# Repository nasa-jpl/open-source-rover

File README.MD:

# JPL Open Source Rover Project
The JPL Open Source Rover is an open source, build it yourself, scaled down version of the 6 wheel rover design that JPL uses to explore the surface of Mars. The Open Source Rover is designed almost entirely out of consumer off the shelf (COTS) parts. This project is intended to be a teaching and learning experience for those who want to get involved in mechanical engineering, software, electronics, or robotics.

## About the Project

### Motivation
JPL is always looking to inspire the next generation of scientists, engineers, and roboticists to help us explore and learn about our solar system (and beyond!). We release the plans for this rover as a way to try and give budding enthusiasts a fun robotics project that will help teach them and get them involved in robotics sooner and at a lower cost. 

### Specifications & Technical Attributes

The specific attributes of the robot you build will depend slightly on the type of electronics and motors you buy for the system.  The numbers shown below are for the version of the robot that contains exactly the parts that we suggest in our build documents and parts list. Below, you can see which parts could be changed for which spec upgrades.

| Attribute	                                | Value [imperial]         | Value [SI]             |
| ----------                                |:-----:                   | :-------------:        |
| Weight                                    | 28 [lbs]                 | 12.7 [kg]              |
| Footprint                                 | 24x14 [in]               | 60.96x30.48 [cm]       |
| Battery Capacity                          | 5200 [mAh]               | 5200 [mAh]             |
| Battery Discharge Rate                    | 8 [A]                    | 8 [A]                  |
| Nominal Current Draw                      | 1.2 [A]                  | 1.2 [A]                |
| Operating time                            | 5 [hrs] (continual use)  | 5 [hrs] (continual use)|
| Approximate Max speed                     | 68.8 [in/s]              | 1.75 [m/s]             |
| Maximum 90 deg vertical scale             | 12 [in]                  | 30.48 [cm]             | 
| Maximum height differential between sides | 14 [in]                  | 35.56 [cm]             |
| Communication (in this guide)             | Bluetooth app (Android only) and Xbox Controller| |
| Cost                                      | ~ $2,500                 |                        |

Again, the above statistics depend on which components you select when buying parts. One potential change is for the motors; you can, for example, select higher RPM motors (to drive your rover faster) at the sacrifice of max stall torque, which would potentially limit your rover's ability to climb. A selection of motors that would integrate easily with the rest of the suggested rover design can be found at [GoBilda](https://www.gobilda.com/5202-series-yellow-jacket-planetary-gear-motors/).

### Features
This rover is designed to function similarly to the 6 wheel rover designs on Mars and employs a few of the major driving mechanics that the mars rovers use to traverse rocky surfaces:
 * __Rocker-Bogie:__ The Rocker-Bogie suspension system allows all 6 wheels to continually be in contact with the ground while climbing over obstacles
 * __Differential Pivot:__ Allows weight to be mechanically offloaded from one side of the rover to the other while climbing
 * __6-Wheel Ackerman Steering:__ Driving and steering/turning mechanism that governs where the wheels point and how fast each of them will move.

We chose a Raspberry Pi to be the "brain" of this rover for its versatility, accessibility, simplicity, and ability to add and upgrade your own modifications. Any method with which you can communicate with a Raspberry Pi (bluetooth, WiFi, USB devices, etc) can be interfaced into the control system of the robot. 

In addition, here are the open communication ports and hardware on the Raspberry Pi:
 * 4 USB ports (3 if using Xbox controller)
 * RPi Camera port
 * 1 I2C Bus (0 if using LED Matrix screen)
 * 2 SPI Bus (1 if using LED Matrix screen)
 * 3.5mm Audio Jack
 * 13 GPIO pins (6 if using LED Matrix screen)

Using the above ports, you could theoretically drive the rover autonomously from the camera, via a USB dongle attached to anything (your own video game controller, a USB microphone, or many others... be creative!), or through any interface using the Pi's GPIO ports (distance sensors, accelerometers, and much more).  We've only given you two simple ways to control the rover to start... we want you to come up with even more!

For the power system of the rover, there is also ample spare power which can be used for your own addons and upgrades.  See the [Electrical subsystem documentation](Electrical/) for more specific details.

### Maintenance Status

As an open-source hardware project, the rover is continuously improving. Please check ongoing [projects](https://github.com/nasa-jpl/open-source-rover/projects), [issues](https://github.com/nasa-jpl/open-source-rover/issues), [pull requests](https://github.com/nasa-jpl/open-source-rover/projects), and the forum (see below) to see if any big changes are expected soon.

We are changing documentation from LaTeX to MarkDown to facilitate contributions. Some instructions might be in PDF format while other might be a `README.md` file rendered in GitHub. To print out a MarkDown page, consider using an extension like [GitHub Markdown Printer](https://chrome.google.com/webstore/detail/github-markdown-printer/fehpdlpmcegfpbkgcnaleindodeegapk?hl=en)

### Online 3D Model

Huge thanks to @toebes for building out an Onshape model of the Open Source Rover!!  That model can be viewed at https://cad.onshape.com/documents/5c358484057fc4c01d5e5803/w/bdf583acdf29d75695be5fbc/e/e3eb7193ecdec5b0a710978b.

The model above includes the state of the rover at each individual step throughout our build instructions!  Therefore, you should be able to reference the online 3D model in addition to the photos in the build instructions as you are building to ensure your build is going well. NOTE: The most updated model and single source of truth are the SolidWorks assemblies.

### Other Resources
In addition to this repository which holds all the documentation for this project, there are two additional websites tied to this project. One is a landing site which holds general information and an overview of the rover and how it works:

https://opensourcerover.jpl.nasa.gov

There is also a user-run forum to help facilitate discussion about the project.

**__Note: JPL and Caltech have no official affiliation with this forum; it is run by individuals of the general public.__**

On this forum, you can ask questions if you need help or clarification on any aspects of the project.  Additionally, you can post and promote any modifications or addons that you have created on this project. We highly encourage additions and modifications to be posted on the forum so that this project and community can grow.

https://www.tapatalk.com/groups/jpl_opensource_rover/

### Skills Necessary
This project has elements in mechanical assembly/fabrication, uses a host of electrical components, and has software that will run it all. In order to complete this project, you will need to have some experience in the following:
 * __Fabrication/Machining:__ Although most the parts are COTS there are a few modifications necessary to adapt them to the project. These modifications will be in the form of 
   * Metal cutting using band saw/dremel
   * Drilling using drill press/hand drill
   * Filing and sanding for part cleanup
   * General Fabrication/Machining Safety
 * __Electronics:__ This project uses components like motors, motor controllers, and batteries. It will be important to have experience with the following electrical processes.
   * Soldering
   * Electrical debugging
   * Wiring
   * Electrical Safety
 * __Software:__ The rover's brain is a Raspberry Pi.  Included in this repository is all the software ready to run the rover, but some  knowledge is required for getting everything up and ready on the Raspberry Pi:
   * Basic Linux familiarity
   * Basic Python familiarity

Most of the above are skills that you can learn and pick up fairly quickly from watching videos and doing research on the internet, and throughout the project we try to give supplemental information on some of these as well.  See the build documents for more information.

### Tools Necessary
This project assumes you have some standard tools to help assemble the project. If you do not have any of the optional tools, we provide examples of online services that you can use to have the parts fabricated and sent to you.

#### Mandatory tools
 * SAE Hex Key set
 * SAE Wrench set
 * Pliers
 * Wire Snips
 * Wire Strippers
 * Solder Iron
 * Solder
 * Digital Multimeter
 * Hand Drill or Drill Press
 * Dremel, Band saw, or hand saw
 * Items for operating a Raspberry Pi (Keyboard, mouse, monitor, 5V micro USB power adapter)
 
 Here is [an Amazon list of some of the tools that may be useful](http://a.co/gnoN2LW)

#### Optional Tools
 * 3D printer
 * Laser Cutter
 * Power Supply (to test without using battery)

### Expected time commitment
In our experience, this project takes no less than 200 person-hours to build, and depending on the familiarity and skill level of those involved could be significantly more. Experienced builders may be able to build this project in this amount of time.  However, this project is generally meant to be a teaching and learning tool.  Throughout the documentation, we try to give supplemental information for those who might be new to this kind of project.

# Disclaimer
**Reference herein to any specific commercial product, process, or service by trade name, trademark, manufacturer, or otherwise, does not constitute or imply its endorsement by the United States Government or the Jet Propulsion Laboratory, California Institute of Technology. Government sponsorship acknowledged.**

**By downloading, cloning, or otherwise using the contents of this repository, you agree to the terms specified in the attached [DISCLAIMER.txt file](/DISCLAIMER.txt).**

## Getting Started

### Folder organization

The main /osr/ folder contains all of the documentation and information necessary for the project, broken down into the 3 main sections: Mechanical, Electrical, and Software. Each of these sections is meant to be relatively self contained and should be fairly parallelizable, meaning that they could be completed simultaneously by different groups. There is a README.md in each section to help you navigate the information in that section. 

### Ordering parts

#### Parts Lists
The [Master Parts List](parts_list/master_parts_list_raw.csv) contains all the parts necessary to build the entirety of the robot as it is listed in our documentation. We recognize that you may want to change, add, and redesign some sections, so each of the individual build sections also contain a parts list for that corresponding section of the project. *Note that these individual parts list recommend buying quantities necessary __only for that section__.  Be sure to assess the quantities you need for common items (particularly screws, nuts, bolts, and other common hardware) if you are changing subassemblies.*

##### Cart Share
In order to help this ordering process we have compiled a few links of a large number of these together already, if you wish to build exactly what is in our build documentation. Note that some of these parts might not be available or outdated. Please check the master parts list for the most up-to-date list of items.

|[McMaster](https://www.mcmaster.com/order/rcvRtedOrd.aspx?ordid=5887891246&lnktyp=txt)|[Amazon](https://www.amazon.com/gp/registry/wishlist/3ELV1FY8J7ZYP/ref=cm_sw_em_r_z_g__wb)|[Pololu](https://www.pololu.com/wishlist/1J10953)|[Adafruit](https://www.adafruit.com/wishlists/460400)|
|---|---|---|---|

**Digikey:** 
The Bill of Materials folder contains (currently just one) Bill of materials file for a specific vendor. We are searching for better ways to help with the ordering process, however for now the easiest way is to take the [Digikey Bill of Materials](Bill%20of%20Materials%20Files/Digikey_BOM.csv) and upload it to [Digikey](https://www.digikey.com/). You can find the "BOM Manager" on their homepage and then start a new BOM, where you can upload this file.  

#### 3D printing and Laser cutting

In addition to ordering all of the parts on the parts list, we recommend that some pieces be 3D printed and laser cut. If you do not have access to a 3D printer or laser cutter, we've added some online services as examples for where you can get those manufactured and shipped to you. You'll find instructions on this in the [Body Build Doc](Mechanical/Body%20Assembly/Body%20Build%20Doc.pdf),  [Corner Steering Build Doc](Mechanical/Corner%20Steering/Corner%20Steering%20Build%20Doc.pdf), and [Head Assembly Build Doc](Mechanical/Head%20Assembly/Head%20Assembly%20Build%20Doc.pdf).

#### Printed Circuit Boards (PCBs)
The main electrical system of this rover relies on a custom printed circuit board (PCB) that handles the routing between the majority of the electrical components.  This board greatly simplifies the build process and eliminates the need for you to route all the wires yourself. You can find the PCB board files at [PCB Files](Electrical/PCB/). These can be ordered at [JLCPCB](https://jlcpcb.com/) by dropping each of the .zip files (these .zip files contain "gerber" files, a typical file format for PCB boards). 

### Rover Build Roadmap

Above is an example roadmap of how you can build the rover and which parts of the build are dependant on the other sections. It is broken down into 5 stages:
 * __Stage 1:__ Start getting all the parts!  
 
 * __Stage 2:__ Once you have all the parts, everything in stage 2 can be completed in parallel. It is *highly* recommended to start on the electrical testing of components outside the robot before doing any electrical work inside the completed robot body. You can also work on the software at any stage between here and the end.

 * __Stage 3:__ During stage 3, the mechanical subassemblies should all be assembled and start to be integrated together.  There should be some amount of testing done on the electrical system, as well as some progress on the software. 

 * __Stage 4:__ The rover is mechanically built and all subassemblies integrated together.  During stage 4, you begin the integration of the electrical components and the various power and data wires that run throughout the rover.

 * __Stage 5:__ Once the electronics are all powered and communicating, you need to test and calibrate all the motors in the system.

 * __Stage 6:__ After everything has been tested and calibrated and the software is up and running, the robot will be fully functioning and built!

 * __Stage 7:__ Add your own upgrades! We chose Raspberry Pi as the brain of the project so that it should be easy to add, change, and upgrade to build exciting things on top of this already cool robot.  Some upgrade ideas to get you brainstorming: sonar for collision detection, IMU for orientation / closed-loop driving / obstacle mapping, camera for object identification and tracking, sensor packages (temperature, pressure, humidity), solar panels, or even a robotic arm!

## Happy building!!
If you have any questions or run into problems during your build, please search for answers and/or reach out on the [forum](https://www.tapatalk.com/groups/jpl_opensource_rover/).

## Releases
The rover has undergone some major changes since its initial release.  The resources and information in this repository (on the master branch) will always be the most up-to-date information about the rover.  However, if you are interested in older versions of the rover, you can see legacy releases of the OSR at https://github.com/nasa-jpl/open-source-rover/releases

 ## Project Team
 ### Project Lead:
 Michael (Mik) Cox
 ### Development Team:
 Eric Junkins and Olivia Lofaro
 ### Special Thanks To:
 Magdy Bareh, Michelle Viotti, Tom Soderstrom, Dave Gallagher, Jim Rinaldi, Molly Bittner, Christine Fuller, Billy Allen, and Charles Dandino

## Additional Projects!
We recognize that there might be a some individuals, hobbyists, and groups that might be hesitant or unable to build the Open Source Rover due to skills/tools necessary, or budgetary constraints. We'd like to give the information to a similar project that was designed by someone who was inspired after participating in our open source rover beta group to design one for around $500, and heavily utilizing 3D printing. We think this project would be especially great as a hobby project, and appropriate for those just getting into some of these areas, or someone looking to spend a little less money. 

https://hackaday.io/project/158208-sawppy-the-rover

https://github.com/Roger-random/Sawppy_Rover

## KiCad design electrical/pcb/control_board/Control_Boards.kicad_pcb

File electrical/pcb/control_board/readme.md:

# Notes on the schematic (Control Board.sch)
    
- for library part ED2989-ND-USB, made VCC and GND passive because these are _alternative_ ways to power the +5V bus, and the electrical rules check-in kicad doesn't allow multiple power output sources for the same bus. Normally this bus is powered by the battery and voltage regulators.
- have to use a PWR_FLAG on the +BATT bus because this power net is not output from the battery directly, it's only available after a series of passive components (diode, fuse)
- also, doesn't really make sense to mark the battery connector ground pin as a "power output", so use PWR_FLAG for GND bus as well
- the 3.3v bus is not actaully powered; RPi's get power on the 5v bus
- We need separate power buses on the two boards, thus we created different power port symbols (e.g. the little triangle that says "GND")
    - the ports on the motor board are post-fixed "\_motor"
    - the ports on the brain board are post-fixed "\_brain"
    - We need different power ports because they function as a "global label" that can be seen across all sheets in a single schematic. So it's important to have different names. 
    - Note it's different for "net labels" - those are local in scope, to the given sheet
    - see https://forum.kicad.info/t/understanding-power-port-components/8945/14 for more background

# Important things to keep in mind when updating schematics

- make sure you're being cleanly about updating symbols in the schematic
    - you should update them in the JPL_Robotics_Lib.lib file, then pull those changes into the local schematic file in kicad
- if kicad creates "cache" or "rescue" libarary files, think before committing those to git. 
    - cache files _should_ be okay, but that's unclear. Ask someone before adding those to git versioning.
    - rescue files _should not_ be commited - but that's also unclear. Ask someone before adding those to git versioning.
- Reference Designators
    - it's important to retain the same reference designators (e.g. J12, U1, C3, etc) when revving the PCB - a lot of the discussion in the open source rover forums have referenced components by the reference designator, so that's a useful well-known name.
    - whenever annotating reference designators in kicad (with `Annotate Schematic...` ), make sure to check `keep existing annotations`
    - of course, if new components are added to the PCB schematic, these will need new completely designators. It's fine to use auto numbering for these.
    - in the worst case, you can always go into the .sch file and fix things by hand in a text editor

# Components

## LM358

- Why do we use these?
    - for buffering the raw encoder signals
    - [voltage follower layout](https://www.allaboutcircuits.com/video-tutorials/op-amp-applications-voltage-follower)
- [datasheet](https://www.ti.com/lit/ds/symlink/lm358.pdf?ts=1619014149430&ref_url=https%253A%252F%252Fwww.ti.com%252Fproduct%252FLM358)
    - see table 6-1 for pin functions

## Roboclaw

- [Datasheet](https://downloads.basicmicro.com/docs/roboclaw_datasheet_2x30A.pdf](https://downloads.basicmicro.com/docs/roboclaw_datasheet_2x30A.pdf)
    - see page 5 and 6
- Pins
    - We don't use the encoder power (+/-, "PWR1/2" in the jpl robotics library) connections on the roboclaw pin header because we supply this via the screw terminals
    
## Raspberry Pi

- [Datasheet](https://www.raspberrypi.org/documentation/hardware/raspberrypi/bcm2711/rpi_DATA_2711_1p0_preliminary.pdf)
- For EEPROM ID SD and SC
    - See page 9 of the datasheet
    - SD is i2c clock (so this pin is set to output)
    - SD is i2c data (so this pin is set to bi-directional)

## Voltage regulators

- 12V
    - [Datasheet](https://www.pololu.com/product/2855)
- 5V
    - [Datasheet](https://www.pololu.com/product/2851)

## Inter-board connectors

- Male
    - PEC10DAAN
    - [Digikey](https://www.digikey.com/en/products/detail/PEC10DAAN/S2012E-10-ND/860601?utm_campaign=buynow&utm_medium=aggregator&curr=usd&utm_source=octopart)
    - [Summary drawing](https://drawings-pdf.s3.amazonaws.com/C10419.pdf)
- Female
    - PPTC102LFBN-RC
    - [Digikey](https://www.digikey.com/en/products/detail/PPTC102LFBN-RC/S7078-ND/810216?utm_campaign=buynow&utm_medium=aggregator&curr=usd&utm_source=octopart)
    - [Summary drawing](https://drawings-pdf.s3.amazonaws.com/10492.pdf)

## Secondary E-stop (e_stop 2) header

- PPTC021LFBN-RC
- [Digikey](https://www.digikey.com/en/products/detail/PPTC021LFBN-RC/S7000-ND/810142?utm_campaign=buynow&utm_medium=aggregator&curr=usd&utm_source=octopart)
- [Summary drawing](https://drawings-pdf.s3.amazonaws.com/10492.pdf)

## Adafruit INA260 headers

- The ina260 
    - https://www.adafruit.com/product/4226#technical-details
    - [pin details](https://learn.adafruit.com/assets/77678)
- 8 pin header
    - PEC08SAAN
    - [Digikey](https://www.digikey.com/en/products/detail/PEC08SAAN/S1012E-08-ND/859161?utm_campaign=buynow&utm_medium=aggregator&curr=usd&utm_source=octopart)
    - [Summary drawing](https://drawings-pdf.s3.amazonaws.com/C10436.pdf)
    - Don't need to connect vbus because we're doing high side sensing
- 2 pin header
    - PEC02SAAN
    - [Digikey](https://www.digikey.com/en/products/detail/sullins-connector-solutions/PEC02SAAN/859155?s=N4IgTCBcDaIAoFEDCAGMBlAgpgciAugL5A)
    - note! This header is actually 0.1" pitch, but we need 0.2" pitch. So the builder will have to go in and manually cut the pins apart. Shouldn't be too hard though.
    - for this reason, using a custom footprint with 0.2" spacing

## Adafruit 16-Channel Servo Driver

- 6 pin header
    - PPTC061LFBN-RC
    - [Digikey](https://www.digikey.com/en/products/detail/sullins-connector-solutions/PPTC061LFBN-RC/810145?s=N4IgTCBcDaIApwCoGEAMA2AjAGQGICEA5AWgCVkQBdAXyA)
- Motor output headers
    - PPTC041LFBN-RC
    - [Digikey](https://www.digikey.com/en/products/detail/PPTC041LFBN-RC/S7002-ND/810144?utm_campaign=buynow&utm_medium=aggregator&curr=usd&utm_source=octopart)
    - 3 of them for each section of 4 output channels on the servo driver board
- note that we don't need to connect the two pin power header, because we aren't routing power through the servo controller board, we're exclusively providing it through the control board

## Corner servo motor connectors

- 3 pin header
    - [Digikey](https://www.digikey.com/en/products/detail/PPTC031LFBN-RC/S7001-ND/810143?utm_campaign=buynow&utm_medium=aggregator&curr=usd&utm_source=octopart)

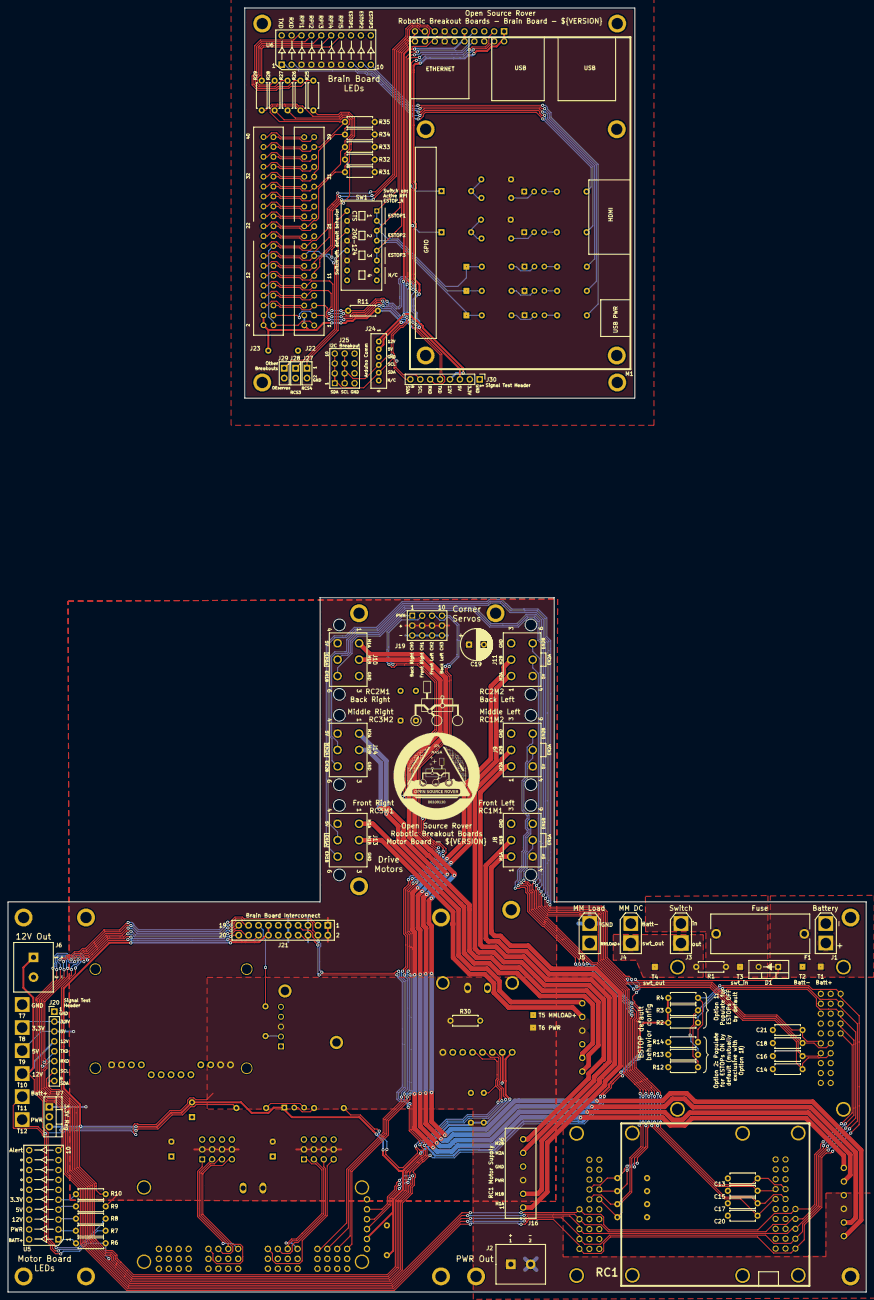
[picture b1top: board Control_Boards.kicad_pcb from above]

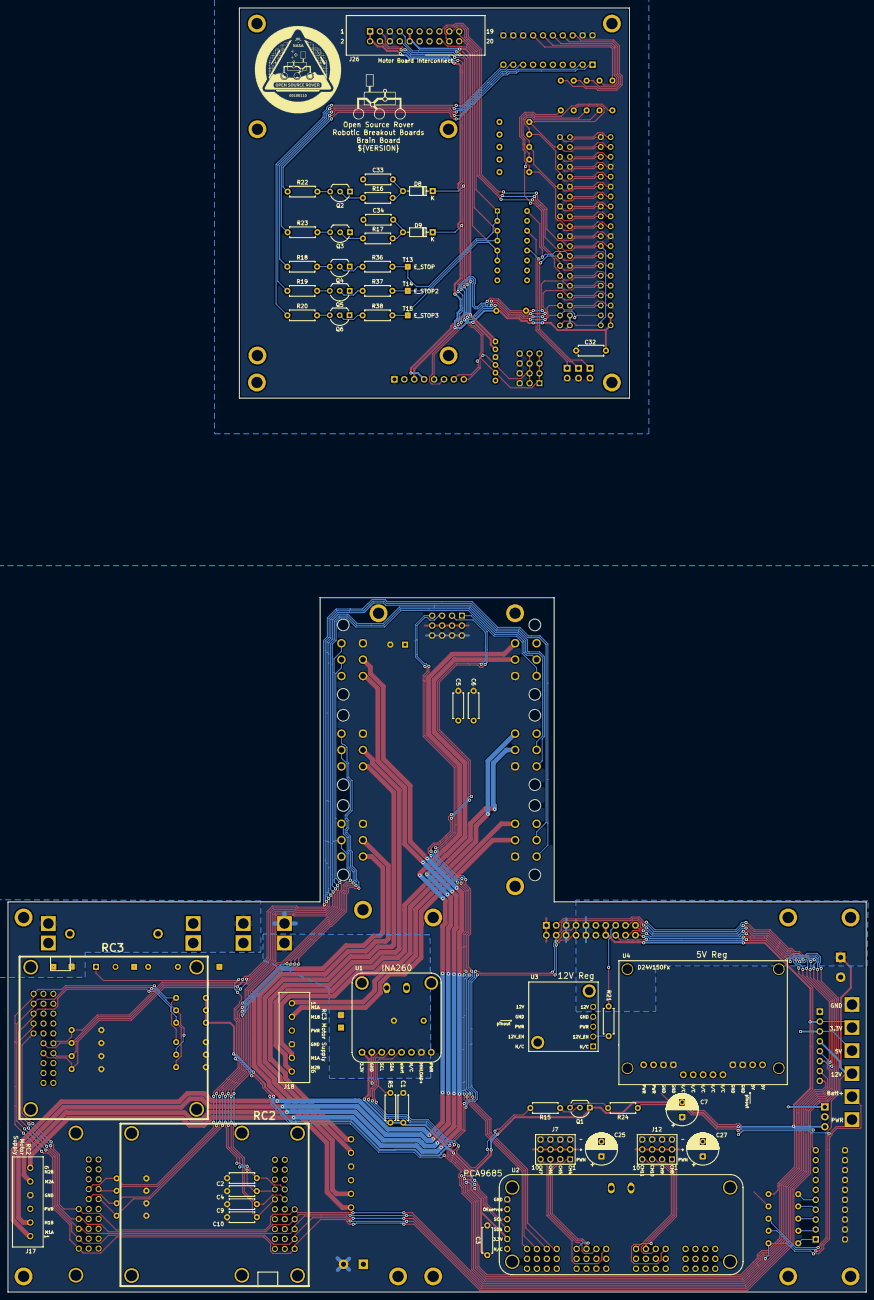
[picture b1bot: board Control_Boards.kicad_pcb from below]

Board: 2 copper layers, 220.0 x 329.2 mm, 148 parts (51 on the bottom side), 125 nets.

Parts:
C1, C3, C5, C6, C32: 100nf; R_Axial_DIN0207_L6.3mm_D2.5mm_P7.62mm_Horizontal
C2, C4, C9, C10, C13, C14, C15, C16, C17, C18, C20, C21, C33, C34: 10nf; R_Axial_DIN0207_L6.3mm_D2.5mm_P7.62mm_Horizontal
C7: 10uf; CP_Radial_D8.0mm_P3.80mm
C19, C25, C27: 100uf; CP_Radial_D8.0mm_P3.80mm
D1: D; 497-2738-5-ND
D8, D9: 1N4148; D_DO-35_SOD27_P7.62mm_Horizontal
F1: Fuse; 696108003002_5x20_fuseholder
J1, J5: XT30-M; AMASS_XT30U-M_1x02_P5.0mm_Vertical
J2, J6: ED2580-ND
J3, J4: XT30-F; AMASS_XT30U-F_1x02_P5.0mm_Vertical
J7, J12, J19: TSW-104-07-F-T; SSW-104-01-F-T
J8, J9, J10, J11, J13, J14: Molex_172675-0613
J16, J17, J18: 277-11404-ND
J20, J30: PEC08SAAN; PinHeader_1x08_P2.54mm_Vertical
J21: PPTC102LFBN-RC
J22, J23: S9175-ND_rpi_breakout; S9175-ND
J24: 6posheader; 455-1708-ND
J25: SSW-104-01-F-T
J26: WM6548-ND
J27, J28, J29: PPTC021LFBN-RC
LOGO1, LOGO2: patch_silkscreen; patch_logo_scaled
M1: Mounting_Holes; raspberry_pi_3b
MH1, MH2, MH3, MH4, MH5, MH6, MH7, MH8, MH17: #4THRU-HOLE
MH9, MH10, MH11, MH12, MH13, MH14, MH15, MH16: brain_board_mounting_hole
Q1, Q2, Q3, Q4, Q5, Q6: 2N3906; TO-92_Inline_Wide
R1, R6, R7: 1k; R_Axial_DIN0207_L6.3mm_D2.5mm_P7.62mm_Horizontal
R2, R3, R4, R5, R11, R12, R13, R14, R31, R32, R33, R34, R35: 4.7k; R_Axial_DIN0207_L6.3mm_D2.5mm_P7.62mm_Horizontal
R8: 680; R_Axial_DIN0207_L6.3mm_D2.5mm_P7.62mm_Horizontal
R9: 220; R_Axial_DIN0207_L6.3mm_D2.5mm_P7.62mm_Horizontal
R10: 100; R_Axial_DIN0207_L6.3mm_D2.5mm_P7.62mm_Horizontal
R15, R16, R17, R36, R37, R38: 10k; R_Axial_DIN0207_L6.3mm_D2.5mm_P7.62mm_Horizontal
R18, R19, R20, R22, R23, R24: 68; R_Axial_DIN0207_L6.3mm_D2.5mm_P7.62mm_Horizontal
R21, R30: 0; R_Axial_DIN0207_L6.3mm_D2.5mm_P7.62mm_Horizontal
R25, R26, R27, R28, R29: 82; R_Axial_DIN0207_L6.3mm_D2.5mm_P7.62mm_Horizontal
RC1, RC2, RC3: RoboClaw; roboclaw_mount
SW1: CT206124-ND; CTS-206-124
T1, T2, T3, T4, T5, T6, T13, T14, T15: test_point
T7, T8, T9, T10, T11, T12: test_point; test_point_hole
U1: INA260
U2: PCA9685; PCA9685_servo_controller
U3: D24V22Fx; D24V22Fx_regulator
U4: D24V150Fx
U5, U6: DC10CGKWA; DC7G3HWA_led_array
U7: MIC2937A-3.3WT; TO-220-3_Vertical
y1, y2: rover_silkscreen; rover_image

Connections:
+3.3V_brain: C33.1, C34.1, J26.13, J26.14, J30.2, Q2.1, Q3.1, Q4.1, Q5.1, Q6.1, R31.2, R32.2, R33.2, R34.2, R35.2, SW1.4, SW1.8, SW1.12, U6.3, U6.4, U6.5, U6.6, U6.7
+3.3V_motor: C1.2, C3.1, C7.2, J20.2, J21.13, J21.14, Q1.1, R2.2, R3.2, R4.2, R5.1, R10.2, T8.1, U1.1, U2.2, U7.3
+5V_brain: C32.1, J22.2, J22.4, J23.2, J23.4, J24.2, J26.1, J26.2, J30.3, R11.2
+5V_motor: C5.1, C6.1, C19.1, C25.2, C27.2, J7.2, J7.5, J7.8, J7.11, J8.4, J9.4, J10.4, J11.4, J12.2, J12.5, J12.8, J12.11, J13.4, J14.4, J19.2, J19.5, J19.8, J19.11, J20.3, J21.1, J21.2, R9.2, T9.1, U2.7, U4.12, U4.13, U7.1
+12V_brain: J24.1, J26.9, J26.10, J30.4
+12V_motor: J6.1, J20.4, J21.9, J21.10, R8.2, T10.1, U3.5
/Brain Board/3.3V_rpi: J22.1, J22.17, J23.1, J23.17
/Brain Board/12V_EN: J22.18, J23.18, J26.15
/Brain Board/ESTOP_LED_1: R18.1, U6.8
/Brain Board/ESTOP_LED_2: R19.1, U6.9
/Brain Board/ESTOP_LED_3: R20.1, U6.10
/Brain Board/ESTOP_in_1_pi: J22.16, J23.16, SW1.2
/Brain Board/ESTOP_in_2: J27.1, SW1.6
/Brain Board/ESTOP_in_3: J28.1, SW1.10
/Brain Board/E_STOP: J26.19, R36.2, SW1.1, SW1.3, T13.1
/Brain Board/E_STOP2: J26.20, R37.2, SW1.5, SW1.7, T14.1
/Brain Board/E_STOP3: J26.16, R38.2, SW1.9, SW1.11, T15.1
/Brain Board/OEservos: J22.15, J23.15, J26.18, J29.1
/Brain Board/RPI_LED_1: J22.22, J23.22, R25.1, R31.1
/Brain Board/RPI_LED_2: J22.37, J23.37, R26.1, R35.1
/Brain Board/RPI_LED_3: J22.29, J23.29, R27.1, R33.1
/Brain Board/RPI_LED_4: J22.31, J23.31, R28.1, R34.1
/Brain Board/RPI_LED_5: J22.11, J23.11, R29.1, R32.1
/Brain Board/RXD: D9.1, J22.10, J23.10, J26.4, J30.6, R11.1
/Brain Board/RXD_LED: R23.1, U6.2
/Brain Board/SCL_rpi: J22.5, J23.5, J24.4, J25.2, J25.5, J25.8, J25.11, J26.7, J30.7
/Brain Board/SDA_rpi: J22.3, J23.3, J24.5, J25.1, J25.4, J25.7, J25.10, J26.8, J30.8
/Brain Board/TXD: D8.1, J22.8, J23.8, J26.3, J30.5
/Brain Board/TXD_LED: R22.1, U6.1
/Brain Board/X_RPI_EEPROM_IDSC: J22.28, J23.28
/Brain Board/X_RPI_EEPROM_IDSD: J22.27, J23.27
/Brain Board/X_RPI_GPIO12: J22.32, J23.32
/Brain Board/X_RPI_GPIO13: J22.33, J23.33
/Brain Board/X_RPI_GPIO16: J22.36, J23.36
/Brain Board/X_RPI_GPIO19: J22.35, J23.35
/Brain Board/X_RPI_GPIO20: J22.38, J23.38
/Brain Board/X_RPI_GPIO21: J22.40, J23.40
/Brain Board/X_RPI_GPIO_GCLK: J22.7, J23.7
/Brain Board/X_RPI_GPIO_GEN1: J22.12, J23.12
/Brain Board/X_RPI_SPI_CE0_N: J22.24, J23.24
/Brain Board/X_RPI_SPI_CE1_N: J22.26, J23.26
/Brain Board/X_RPI_SPI_CLK: J22.23, J23.23
/Brain Board/X_RPI_SPI_MISO: J22.21, J23.21
/Brain Board/X_RPI_SPI_MOSI: J22.19, J23.19
/Brain Board/alert: J22.13, J23.13, J26.17
/Motor Board/12V_EN: J21.15, R21.2
/Motor Board/ALERT_LED: R24.1, U5.10
/Motor Board/BATT+: D1.1, F1.1, J1.2, R6.2, T1.1, T11.1
/Motor Board/BATT-: J1.1, J4.1, T2.1
/Motor Board/E_STOP: J21.19, R2.1, R12.1, RC1.23, RC2.23, RC3.23
/Motor Board/E_STOP2: J21.20, R3.1, R13.1, RC1.24, RC2.24, RC3.24
/Motor Board/E_STOP3: J21.16, R4.1, R14.1, RC1.25, RC2.25, RC3.25
/Motor Board/MMLOAD+: J5.2, R30.2, T5.1, U1.7, U1.9
/Motor Board/OEservos: J21.18, U2.5
/Motor Board/RC1EN1A: C13.1, J8.5, RC1.7
/Motor Board/RC1EN1B: C15.1, J8.6, RC1.8
/Motor Board/RC1EN2A: C17.1, J9.5, RC1.9
/Motor Board/RC1EN2B: C20.1, J9.6, RC1.10
/Motor Board/RC1M1A: J8.1, J16.1
/Motor Board/RC1M1B: J8.2, J16.2
/Motor Board/RC1M2A: J9.1, J16.5
/Motor Board/RC1M2B: J9.2, J16.6
/Motor Board/RC2EN1A: C2.1, J10.5, RC2.7
/Motor Board/RC2EN1B: C4.1, J10.6, RC2.8
/Motor Board/RC2EN2A: C9.1, J11.5, RC2.9
/Motor Board/RC2EN2B: C10.1, J11.6, RC2.10
/Motor Board/RC2M1A: J10.1, J17.1
/Motor Board/RC2M1B: J10.2, J17.2
/Motor Board/RC2M2A: J11.1, J17.5
/Motor Board/RC2M2B: J11.2, J17.6
/Motor Board/RC3EN1A: C14.1, J13.5, RC3.7
/Motor Board/RC3EN1B: C16.1, J13.6, RC3.8
/Motor Board/RC3EN2A: C18.1, J14.5, RC3.9
/Motor Board/RC3EN2B: C21.1, J14.6, RC3.10
/Motor Board/RC3M1A: J13.1, J18.1
/Motor Board/RC3M1B: J13.2, J18.2
/Motor Board/RC3M2A: J14.1, J18.5
/Motor Board/RC3M2B: J14.2, J18.6
/Motor Board/RXD: J20.6, J21.4, RC1.22, RC2.22, RC3.22
/Motor Board/SCL_rpi: J20.7, J21.7, U1.3, U2.4
/Motor Board/SDA_rpi: J20.8, J21.8, U1.4, U2.3
/Motor Board/TXD: J20.5, J21.3, RC1.21, RC2.21, RC3.21
/Motor Board/alert: J21.17, R5.2, R15.2, U1.5
/Motor Board/servo_pwm_ch0: J19.1, U2.9
/Motor Board/servo_pwm_ch1: J19.4, U2.12
/Motor Board/servo_pwm_ch2: J19.7, U2.15
/Motor Board/servo_pwm_ch3: J19.10, U2.18
/Motor Board/servo_pwm_ch4: J7.1, U2.21
/Motor Board/servo_pwm_ch5: J7.4, U2.24
/Motor Board/servo_pwm_ch6: J7.7, U2.27
/Motor Board/servo_pwm_ch7: J7.10, U2.30
/Motor Board/servo_pwm_ch8: J12.1, U2.33
/Motor Board/servo_pwm_ch9: J12.4, U2.36
/Motor Board/servo_pwm_ch10: J12.7, U2.39
/Motor Board/servo_pwm_ch11: J12.10, U2.42
/Motor Board/switch_in: D1.2, F1.2, J3.1, R1.2, T3.1
/Motor Board/switch_out: J3.2, J4.2, R1.1, T4.1
GND_brain: C32.2, J22.6, J22.9, J22.14, J22.20, J22.25, J22.30, J22.34, J22.39, J23.6, J23.9, J23.14, J23.20, J23.25, J23.30, J23.34, J23.39, J24.3, J25.3, J25.6, J25.9, J25.12, J26.5, J26.6, J27.2, J28.2, J29.2, J30.1, U6.11, U6.12, U6.13, U6.19, U6.20
GND_motor: C1.1, C2.2, C3.2, C4.2, C5.2, C6.2, C7.1, C9.2, C10.2, C13.2, C14.2, C15.2, C16.2, C17.2, C18.2, C19.2, C20.2, C21.2, C25.1, C27.1, J2.2, J5.1, J6.2, J7.3, J7.6, J7.9, J7.12, J8.3, J9.3, J10.3, J11.3, J12.3, J12.6, J12.9, J12.12, J13.3, J14.3, J16.4, J17.4, J18.4, J19.3, J19.6, J19.9, J19.12, J20.1, J21.5, J21.6, R12.2, R13.2, R14.2, T7.1, U1.2, U2.6, U2.8, U3.4, U4.3, U4.4, U4.10, U4.11, U5.11, U5.12, U5.13, U5.14, U5.15, U5.16, U5.17, U5.18, U5.19, U5.20, U7.2
unnamed: C33.2, D8.2, R16.2
unnamed: C34.2, D9.2, R17.2
unnamed: Q1.2, R15.1
unnamed: Q1.3, R24.2
unnamed: Q2.2, R16.1
unnamed: Q2.3, R22.2
unnamed: Q3.2, R17.1
unnamed: Q3.3, R23.2
unnamed: Q4.2, R36.1
unnamed: Q4.3, R18.2
unnamed: Q5.2, R37.1
unnamed: Q5.3, R19.2
unnamed: Q6.2, R38.1
unnamed: Q6.3, R20.2
unnamed: R6.1, U5.1
unnamed: R7.1, U5.2
unnamed: R8.1, U5.3
unnamed: R9.1, U5.4
unnamed: R10.1, U5.5
unnamed: R21.1, U3.2
unnamed: R25.2, U6.18
unnamed: R26.2, U6.17
unnamed: R27.2, U6.16
unnamed: R28.2, U6.15
unnamed: R29.2, U6.14
PWR: J2.1, J16.3, J17.3, J18.3, R7.2, R30.1, T6.1, T12.1, U1.8, U1.10, U3.3, U4.1, U4.2

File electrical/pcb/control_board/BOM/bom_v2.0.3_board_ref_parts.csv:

UID,Reference,Name,Quantity,Number to Order,Value,Digi-Key Part,URL,Availability,Notes,Footprint,Datasheet
A1,C2 C4 C9 C10 C13 C14 C15 C16 C17 C18 C20 C21 C33 C34,,14,20,10nf,399-9865-1-ND,https://www.digikey.com/en/products/detail/kemet/C317C103K5R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,,,Resistor_THT:R_Axial_DIN0207_L6.3mm_D2.5mm_P7.62mm_Horizontal,~
A2,C19 C25 C27 C28,,4,10,100uF,399-18272-1-ND,https://www.digikey.com/en/products/detail/kemet/ESK107M050A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,,,Resistor_THT:R_Axial_DIN0207_L6.3mm_D2.5mm_P7.62mm_Horizontal,~
A3,C1 C3 C5 C6 C32,,5,10,100nf,399-14065-1-ND,https://www.digikey.com/en/products/detail/kemet/C322C104K5R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,,,Resistor_THT:R_Axial_DIN0207_L6.3mm_D2.5mm_P7.62mm_Horizontal,~
A4,C7,,1,3,10uf,399-ESK106M050AC3DACT-ND,https://www.digikey.com/en/products/detail/kemet/ESK106M050A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,,,Capacitor_THT:CP_Radial_D8.0mm_P3.80mm,
A5,D1,motor power return diode,1,2,,497-2738-5-ND,https://www.digikey.com/en/products/detail/stmicroelectronic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,,,JPL Robotics:497-2738-5-ND,~
A6,D8 D9,led diode,2,10,1N4148,1655-1N4148CT-ND,https://www.digikey.com/en/products/detail/smc-diode-solutio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,,,Diode_THT:D_DO-35_SOD27_P7.62mm_Horizontal,https://assets.nexperia.com/documents/data-sheet/1N4148_1N4448.pdf
A7,F1,fuse holder,1,1,Fuse Holder,732-11376-ND,https://www.digikey.com/en/products/detail/würth-elektronik/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,,,JPL Robotics:696108003002_5x20_fuseholder,~
A8,J1 J5,male power header,2,"1 pack (J1,J5,J3,J4)",XT30-M,n/a,https://www.amazon.com/gp/product/B0875MBLNH/ref=ppx_yo_dt_b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,,"needs mate, see other page",JPL Robotics:AMASS_XT30U-M_1x02_P5.0mm_Vertical,
A9,J16 J17 J18,phoenix contact header,3,3,WM25701-ND,WM25701-ND,https://www.digikey.com/en/products/detail/molex/0395016006/2735254,,"needs mate, see other page

alternative suppliers: 
- https://www.arrow.com/en/products/5452096/phoenix-contact 
- https://www.digikey.com/en/products/detail/phoenix-contact/5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",JPL Robotics:277-11404-ND,
A10,J7 J12 J15 J19,pwm header,3,4,TSW-104-07-F-T,TSW-104-07-F-T,https://www.digikey.com/en/products/detail/samtec-inc/TSW-10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,,,JPL Robotics:SSW-104-01-F-T,
A11,J20 J30,test pin header,2,4,PEC08SAAN,S1012E-08-ND,https://www.digikey.com/en/products/detail/sullins-connector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,,,Connector_PinHeader_2.54mm:PinHeader_1x08_P2.54mm_Vertical,
A12,J21,interconnect header,1,1,PPTC102LFBN-RC,PPTC102LFBN-RC,https://www.digikey.com/en/products/detail/sullins-connector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,,,JPL Robotics:PPTC102LFBN-RC,
A13,J22 J23,rpi header,2,2,S9175-ND_rpi_breakout,S9175-ND,https://www.digikey.com/en/products/detail/sullins-connector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,,,JPL Robotics:S9175-ND,
A14,J24,arduino header,1,2,6posheader,455-1708-ND,https://www.digikey.com/en/products/detail/jst-sales-america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,,,JPL Robotics:455-1708-ND,
A15,J25,rpi i2c header,1,0,SSW-104-01-F-T,SSW-104-01-F-T-ND,https://www.digikey.com/en/products/detail/samtec-inc/SSW-10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,,Added +1 of TSW-104-07-F-T. Needs cleanup in kicad files,JPL Robotics:SSW-104-01-F-T,
A16,J26,"board interconnect header, brain board side",1,1,kk      ,WM6548-ND,https://www.digikey.com/en/products/detail/molex/0702462001/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,,,JPL Robotics:WM6548-ND,
A17,J27 J28 J29,brain board other breakout header,3,5,PPTC021LFBN-RC,S7000-ND,https://www.digikey.com/en/products/detail/sullins-connector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,,,JPL Robotics:PPTC021LFBN-RC,
A18,J3 J4,female power header,2,"1 pack (J1,J5,J3,J4)",XT30-F,n/a,https://www.amazon.com/gp/product/B0875MBLNH/ref=ppx_yo_dt_b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,,"needs mate, see other page",JPL Robotics:AMASS_XT30U-F_1x02_P5.0mm_Vertical,
A19,J2 J6,power breakout terminal block,2,2,ED2580-ND,ED2580-ND,https://www.digikey.com/en/products/detail/on-shore-technolo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,,,JPL Robotics:ED2580-ND,
A20,J8 J9 J10 J11 J13 J14,drive motor header,6,6,Molex_172675-0613,172675-0613,https://www.digikey.com/en/products/detail/molex/1726750613/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,,"needs mate, see other page",JPL Robotics:Molex_172675-0613,
A21,Q1 Q2 Q3 Q4 Q5 Q6,led bjt transistor,6,10,2N3906,2N3906TAFSCT-ND,https://www.digikey.com/en/products/detail/onsemi/2N3906TA/975255,,,Package_TO_SOT_THT:TO-92_Inline,https://www.onsemi.com/pub/Collateral/2N3906-D.PDF
A22,R10,,1,10,100,CF14JT100RCT-ND,https://www.digikey.com/en/products/detail/stackpole-electro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,,,Resistor_THT:R_Axial_DIN0207_L6.3mm_D2.5mm_P7.62mm_Horizontal,~
A23,R15 R16 R17 R36 R37 R38,,6,10,10k,CF14JT10K0CT-ND,https://www.digikey.com/en/products/detail/stackpole-electro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,,,Resistor_THT:R_Axial_DIN0207_L6.3mm_D2.5mm_P7.62mm_Horizontal,~
A24,R2 R3 R4 R5 R11 R12 R13 R14 R31 R32 R33 R34 R35,,13,25,4.7k,CF14JT4K70CT-ND,https://www.digikey.com/en/products/detail/stackpole-electro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,,,Resistor_THT:R_Axial_DIN0207_L6.3mm_D2.5mm_P7.62mm_Horizontal,~
A25,R21 R30,,2,10,0,CD14ZT0R00CT-ND,https://www.digikey.com/en/products/detail/stackpole-electro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,,,Resistor_THT:R_Axial_DIN0207_L6.3mm_D2.5mm_P7.62mm_Horizontal,
A26,R18 R19 R20 R22 R23 R24,,6,10,68,CF14JT68R0CT-ND,https://www.digikey.com/en/products/detail/stackpole-electro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,,,Resistor_THT:R_Axial_DIN0207_L6.3mm_D2.5mm_P7.62mm_Horizontal,
A27,R25 R26 R27 R28 R29,,5,10,82,CF14JT82R0CT-ND,https://www.digikey.com/en/products/detail/stackpole-electro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,,,Resistor_THT:R_Axial_DIN0207_L6.3mm_D2.5mm_P7.62mm_Horizontal,
A28,R1 R6 R7,,3,10,1k,CF14JT1K00CT-ND,https://www.digikey.com/en/products/detail/stackpole-electro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,,,Resistor_THT:R_Axial_DIN0207_L6.3mm_D2.5mm_P7.62mm_Horizontal,~
A29,R8,,1,10,680,CF14JT680RCT-ND,https://www.digikey.com/en/products/detail/stackpole-electro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,,,Resistor_THT:R_Axial_DIN0207_L6.3mm_D2.5mm_P7.62mm_Horizontal,
A30,R9,,1,10,220,CF14JT220RCT-ND,https://www.digikey.com/en/products/detail/stackpole-electro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,,,Resistor_THT:R_Axial_DIN0207_L6.3mm_D2.5mm_P7.62mm_Horizontal,
A31,RC1 RC2 RC3,roboclaw,3,3,RoboClaw,n/a,https://www.basicmicro.com/Roboclaw-2x7A-Motor-Controller_p_55.html,Available,appears to be sold out everywhere but basicmicro,JPL Robotics:roboclaw_mount,
A32,SW1,estop switches,1,1,CT206124-ND,CT206124-ND,https://www.digikey.com/en/products/detail/cts-electrocompon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,Available,,JPL Robotics:CTS-206-124,
A33,U1,ina260 power measurement unit,1,1,INA260,1528-2955-ND,https://www.digikey.com/en/products/detail/adafruit-industri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,Not available. Use bypass resistor or build breakout board yourself.,"Appears to be sold out everywhere right now. 

Can bypass on the motor board using 0 ohm resistor (R30)

Alternative is to buy the TI chip itself and assemble the adafruit breakout board separately yourself. EagleCAD files here",JPL Robotics:INA260,
A34,U2,pca9685 corner motor driver,1,1,PCA9685,n/a,https://www.mouser.com/ProductDetail/Adafruit/815?qs=GURawfa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,Available,"Alternative sellers:
- rs-online
- https://www.digikey.com/en/products/detail/adafruit-industri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 ",JPL Robotics:PCA9685_servo_controller,
A35,U3,12v regulator,1,1,D24V22F12,n/a,https://www.pololu.com/product/2855,Available,,JPL Robotics:D24V22Fx_regulator,
A36,U4,5v regulator,1,1,D24V150F5,2183-2881-ND,https://www.pololu.com/product/2881,Limited availability. Look for other suppliers if you can't find.,"Alternative sellers:
- https://www.digikey.com/en/products/detail/pololu-corporatio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 
- https://opencircuit.shop/product/5v-15a-step-down-voltage-re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 
- https://www.solarbotics.com/product/51017/ ",JPL Robotics:D24V150Fx,
A37,U5 U6,LED array,2,2,DC10CGKWA,754-2186-ND,https://www.digikey.com/en/products/detail/kingbright/DC10CG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,Available,Used DC7G3HWA originally for v2.0.1 . That's obsolete now.,JPL Robotics:DC7G3HWA_led_array,
A38,U7,3.3v regulator,1,2,MIC2937A-3.3WT,576-2235-ND,https://www.digikey.com/en/products/detail/microchip-technol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,Available,,Package_TO_SOT_THT:TO-220-3_Vertical,

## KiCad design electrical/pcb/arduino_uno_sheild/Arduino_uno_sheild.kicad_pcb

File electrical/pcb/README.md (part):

# Control Board Assembly, v2.0.3

The overall Control Board consists of a Motor Board with a Brain Board mounted on top. These are the instructions to assemble these two separate pcbs and mount them together as the unified control board.

This document goes through the process of assembling and testing the custom
Printed Circuit Boards for the project. 

Note that the images in these instructions are taken from an assembly of the v2.0.1 board. There are minimal differences between v2.0.1 and v2.0.3 - such that it wasn't worth doing another photoshoot for v2.0.3. Make sure to follow the written instructions when in doubt.

## Table of Contents
1. [Part References](#1-part-references)
2. [Schematic and Layout Documentation](#2-schematic-and-layout-documentation)
3. [Motor Board Assembly](#3-motor-board-assembly)
4. [Brain Board Assembly](#4-brain-board-assembly)
5. [Motor Board and Brain Board Mating](#5-motor-board-and-brain-board-mating)
6. [Testing the PCB and wiring for the Drive Motors](#6-testing-the-pcb-and-wiring-for-the-drive-motors)

## 1. Part References 

Check out the [BOM documents](control_board/BOM/v2.0.3)

All parts referenced in these instructions use the schematic "reference designator" from the silk screen on the pcbs. E.g. "C1", "J2", and "R28". You should look up the details of these parts within the [v2.0.3 BOM the board ref parts spreadsheet](control_board/BOM/v2.0.3/bom_v2.0.3_board_ref_parts.csv) or the [v2.0.3 BOM other parts spreadsheet](control_board/BOM/v2.0.3/bom_v2.0.3_other_parts.csv). This will tell you the unique ID of the part that we use for ordering from Digikey + elsewhere, and will also link to pictures of the part on the relevant website.

Generally these instructions have enough images to clearly show and identify the parts, but whenever in doubt the best thing to do is to look up the reference in the BOM spreadsheet.

## 2. Schematic and Layout Documentation

TODO: add versions for v2.0.3

There's documentation of both the schematics (how all the electrical parts logically connect to one another) and the layout (how the parts are physically placed on the boards) in the [control_board/documentation](control_board/documentation) directory

## 3. Motor Board Assembly

|    |
|:-:|
| Figure 3.0: front (left) and back (right) of motor board |

### 3.1 Attach standoffs

Attach M2.5 x 30mm standoffs to the bare board, for ease of future soldering work.

|   |
|:-:|
| Figure 3.1: Standoffs attached |

### 3.2 Solder on power headers and fuse holder

Solder on the XT30 headers for footprints J1, J3, J4, and J5, as well as the fuse holder F1.

Make sure to choose the proper XT30 header for the corresponding J footprint:
- J1: male
- J3: female
- J4: female
- J5: male
See the images to clarify which one is which.

The pins on the XT30 will be slightly smaller than the holes on the board - this is fine, just make sure to use a lot of solder to connect them so there's a good mechanical connection. The soldering should be fairly straightforward once you start. 

|  |
|:-:|
| Figure 3.2: Power headers + fuse holder footprints |

|  |
|:-:|
| Figure 3.3: Power headers + fuse holder attached |

|  |
|:-:|
| Figure 3.4: Power headers and fuse holder attached, zoomed out |

|  |
|:-:|
| Figure 3.5: Close up view of soldered footprints for headers |

### 3.3 Solder resistor R1 and power diode D1

Make sure to attach D1 in the correct orientation!

|  |
|:-:|
| Figure 3.6: Resistor R1 |

|  |
|:-:|
| Figure 3.7: Through hole leads for R1 and D1 |

|  |
|:-:|
| Figure 3.8: R1 and D1 attached |

### 3.4 Test the power connectors

Insert a fuse (part# B1) into the fuse holder (as shown in Figure 3.8 below)

Using the appropriate matching XT30 connectors, connect the power headers to a power supply (or your battery), the main external power switch (part# B9), and the multimeter (part# B10)

Use these diagrams to determine how to wire things together:

When testing with a power supply, provide 14.8V DC and current limit to 1.0A. Just to the left of the main fuse is a XT30 connector labeled "Switch" – this if for the main on/off toggle switch. The XT30 connectors labeled MM Load and MM DC connect to the multimeter box.

> [!Note]
> If you have already installed capacitors on the board, it is normal for power header J5 (MM Load) to briefly beep for less than a second when testing for continuity after soldering the power headers. This occurs because the capacitors momentarily charge. This behavior is expected and does not indicate a short circuit.

 |  |
|:-:|
| Figure 3.9: Power headers connected to the power supply, on/off toggle switch (out of view under the PCB) and multimeter box. |

After testing, make sure to disconnect the power supply.

|  |
|:-:|
| Figure 3.10: Wires connected to power headers |

|  |
|:-:|
| Figure 3.11: Power supply providing 14.8V DC and current limited to 1.0A |

Use a multimeter to test the voltage between test points T4 ("swt_out") and T2 ("Batt-"). This should read the same value as input from the power supply/battery (14.8V)

|  |
|:-:|
| Figure 3.12: Testing the voltage between T4 and T2 |

Also check the voltage shown by the multimeter. This should show the same voltage as well.

|  |
|:-:|
| Figure 3.13: Testing the power input to the multimeter |

### 3.5 Install the INA 260

:exclamation: Before continuing, make sure to disconnect the power supply from the previous step! You should not have the board powered on while installing components. :exclamation:

The INA260 daughter board is used for digital sensing of voltage and current, measurements that the raspberry pi can query over an I2C connection. Unfortunately, it can be hard to find these INA260 parts nowadays - if you can't find one you will need to bypass U1, because it is in the path of the battery positive side supply.

**Option 1: If you have an INA260 daughter board, you should install that in footprint U1 on the bottom side of the motor board.**

See [control_board/README.md](control_board/readme.md) for part numbers for inter-board pins and sockets.

1. Attach 8x1 female header sockets to the eight pads on the bottom side of the INA260 / U1 footprint, as seen in Figure 3.14.  This is sensing the current on the high side of the power, so PWR on the the Motor Board is connected to Vin+ on the INA260, and Vin- on the INA260 is connected to MMLOAD+, which connects to the main power bus of the rover.
2. Attach 3x1 female header socket (cut from a longer Nx1 header) to the two pads on the bottom side of the INA260 / U1 footprint, as seen in Figure 3.14. You'll need to manually remove the center pin, as there is no hole/pad on the brain board.

|  |
|:-:|
| Figure 3.14: Sockets on U1 footprint installed |

3. Attach 8x1 male header pins to the underside of the INA260, as seen in Figure 3.15
4. Remove the center pin from a 3x1 male header pins, and solder to the INA260.

|   |
|:-:|
| Figure 3.15: INA260 Pins installed |

5. Solder across pads A0 and A1 on the INA260 (to set it to use I2C Address 0x45)
6. Insert the INA260 male pins into the U1 female sockets, as shown in Figure 3.16
6. Optionally, install M2.5 x 12mm + 6mm standoffs between the motor board and the INA260.

|  |
|:-:|
| Figure 3.16: Headers on INA260 installed |

**Option 2: If you don't have one, you will need to bypass U1**

TODO: need to update this discussion of bypassing U1 once the layout has been updated

Install a 0 ohm resistor in footprint R30, on the top side of the board

### 3.6 Install 5V bus regulator

This is the power regulator for the 5V line, which powers all the motors.

Install 3 female headers for the daughter board, into U4. You will need a two 4x1's, and a 5x1.

|  |
|:-:|
| Figure 3.17: 5V regulator headers installed |

|  |
|:-:|
| Figure 3.18: 5V regulator installed |

### 3.7 Install 12V bus regulator U3

Solder a 5x1 female header to the U3 footprint, and attach M2.5 x 10mm standoffs between the regulator and motor board

|  |
|:-:|
| Figure 3.19: U3 footprint |

|  |
|:-:|
| Figure 3.20: 12v regulator installed |

|  |
|:-:|
| Figure 3.21: 12v regulator installed (2) |

### 3.8 Install 3.3V bus regulator U7 and decoupling capacitor C7

The 3.3V bus regulator is a linear voltage regulator and is physically much smaller - it comes in the same packaging as diode D1. Make sure to install the regulator in the correct direction as shown in figure 3.23.

Capacitor C7 is the decoupling capacitor for the 3.3v bus. Make sure to install C7 in the proper direction, as shown in figure 3.24. One side of the capacitor has negative polarity indicators on it, that should be installed opposite the "+" sign on the footprint.

|  |
|:-:|
| Figure 3.22: U7 footprint |

|  |
|:-:|
| Figure 3.23: 3.3v regulator installed in U7 |

|  |
|:-:|
| Figure 3.24: Capacitor C7 installed |

### 3.9 Install resistors R15, R24, and BJT transistor Q1

These form the circuit for the alert signal LED logic.

|  |
|:-:|
| Figure 3.25: R15, R24, and Q1 footprints |

|  |
|:-:|
| Figure 3.26: R15, R24, and Q1 installed |

### 3.10 Test all voltage lines

Test all the power buses/voltage lines using the test points on the far left side of the top side of the board (T7 through T12).

The silk screen right of each hole indicates what voltage each test point should be at.

- First, connect the power supply to your board and provide 14.8v (see step 3.4)
- then, use the multimeter to test the voltage at each test point

|  |
|:-:|
| Figure 3.27: testing the 3.3v bus|

|  |
|:-:|
| Figure 3.28: testing the 5v bus |

|  |
|:-:|
| Figure 3.29: testing the 12v bus |

|  |
|:-:|
| Figure 3.30: testing the Batt+ bus (positive lead from the battery) |

|  |
|:-:|
| Figure 3.31: testing the PWR bus (main board power plane, after battery protection circuitry ) |

### 3.11 Install PCA9685 daughter board in U2 footprint and capacitor C3

:exclamation: Before continuing, make sure to disconnect the power supply from the previous step! You should not have the board powered on while installing components. :exclamation:

The PCA9685 is a PWM signal source, which we use as our corner motor controller.

First you will need to install female headers on the motor board, for the PCA9685 daughter board to mate with. You'll need: 
- 6x1 female header
- 3x 2x4 female headers

You **may** use larger headers to fill all the holes in the U2 footprint, but it's not really necessary for the normal working configuration of the motor board. Attach these headers to the appropriate spots in the U2 footprint, as shown in figure 3.32.

|  |
|:-:|
| Figure 3.32: U2 with female headers installed |

You will need to attach male headers to the PCA9685 daughter board, as shown in figure 3.33. 

Also, 5v power is provided to the PCA9685 through the two holes at the top of the U2 header. You have a couple options for this.

**Option 1 - Wires**
To connect these, I soldered 2 small wire leads on the PCA9685 daughter board, and then soldered them on to the motor board once I installed the PCA9685.

**Option 2 - 1x1 Pins/Headers**
The V+ and GND on the PCA9685 don't exactly line up with the GND_motor and +5V_motor pins on the Motor board, but are close enough you can make them connect with two 1x1 pins on the PCA9685 and two 1x1 headers on the Motor board, as shown in figure 3.34.

|  |
|:-:|
| Figure 3.33: Male headers soldered onto PCA9685 daughter board |

|  |
|:-:|
| Figure 3.34: PCA9685 installed in motor board |

Finally install capicator C3 as shown in figure 3.36.

|  |
|:-:|
| Figure 3.35 : C3 installed |

### 3.12 Install resistor R5 and capacitor C1

These are aids for the INA260, and can be left out if the IN260 is not used

|  |
|:-:|
| Figure 3.36: PCA9685 installed in motor board |

### 3.13 Install J21, J20, and resistors R6,R7,R8,R9,R10

J21 is the interconnect header for the brain board, and J20 is a signal test header for the motor board

Use an 8x1 female header for J20.

|  |
|:-:|
| Figure 3.37: Components installed, as viewed from top of board |

### 3.14 Test INA260 installation

To test the INA260, you will follow https://learn.adafruit.com/adafruit-ina260-current-voltage-power-sensor-breakout/arduino, and connect an Arduino to GND, SCL, and SDA on J20.  You'll change the initalization step to
```
 if (!ina260.begin(0x45)) {
```
to account for the I2C bus address.  When you turn your power on, you should see something like this in the Arduino serial terminal:
```
Found INA260 chip
Current: 85.00 mA
Bus Voltage: 14456.25 mV
Power: 1230.00 mW
```

### 3.15 Install resistors R2,R3,R4

|  |
|:-:|
| Figure 3.38: Components installed, as viewed from top of board |

### 3.16 Install Roboclaw standoffs, headers, and capacitors

Now we'll add the parts for roboclaw footprints RC1, RC2, and RC3.

First, install M2.5 x 15mm standoffs for the 3 RC footprints, as shown an figure 3.33 and 3.34. 

Next, solder in the two female headers for each RC footprint. You'll need a 2x10 and a 5x1 for each RC. These should be soldered into the holes on the side of each RC footprint.

Finally, install the following capacitors for each RC footprint:
- RC1: capacitors C13,C15,C17,C20 (figure 3.40). Install on the top side of the board.
- RC2: capacitors C2,C4,C9,C10 (figure 3.39). Install on the underside of the board.
- RC3: capacitors C14,C16,C18,C21 (figure 3.40). Install on the top side of the board.

Technically, you can install the capacitors on either side of the board, but it makes for a cleaner presentation if you install them where their respective "C" labels are on the board.

|  |
|:-:|
| Figure 3.39: C2,C4,C9,C10 installed|

|  |
|:-:|
| Figure 3.40: C13,C15,C17,C20 and C14,C16,C18,C21 installed|

### 3.17 Install motor supply headers J16,J17,J18

Figure 3.41 shows how these should be installed. J16 on the top of the board is installed in the same way.

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
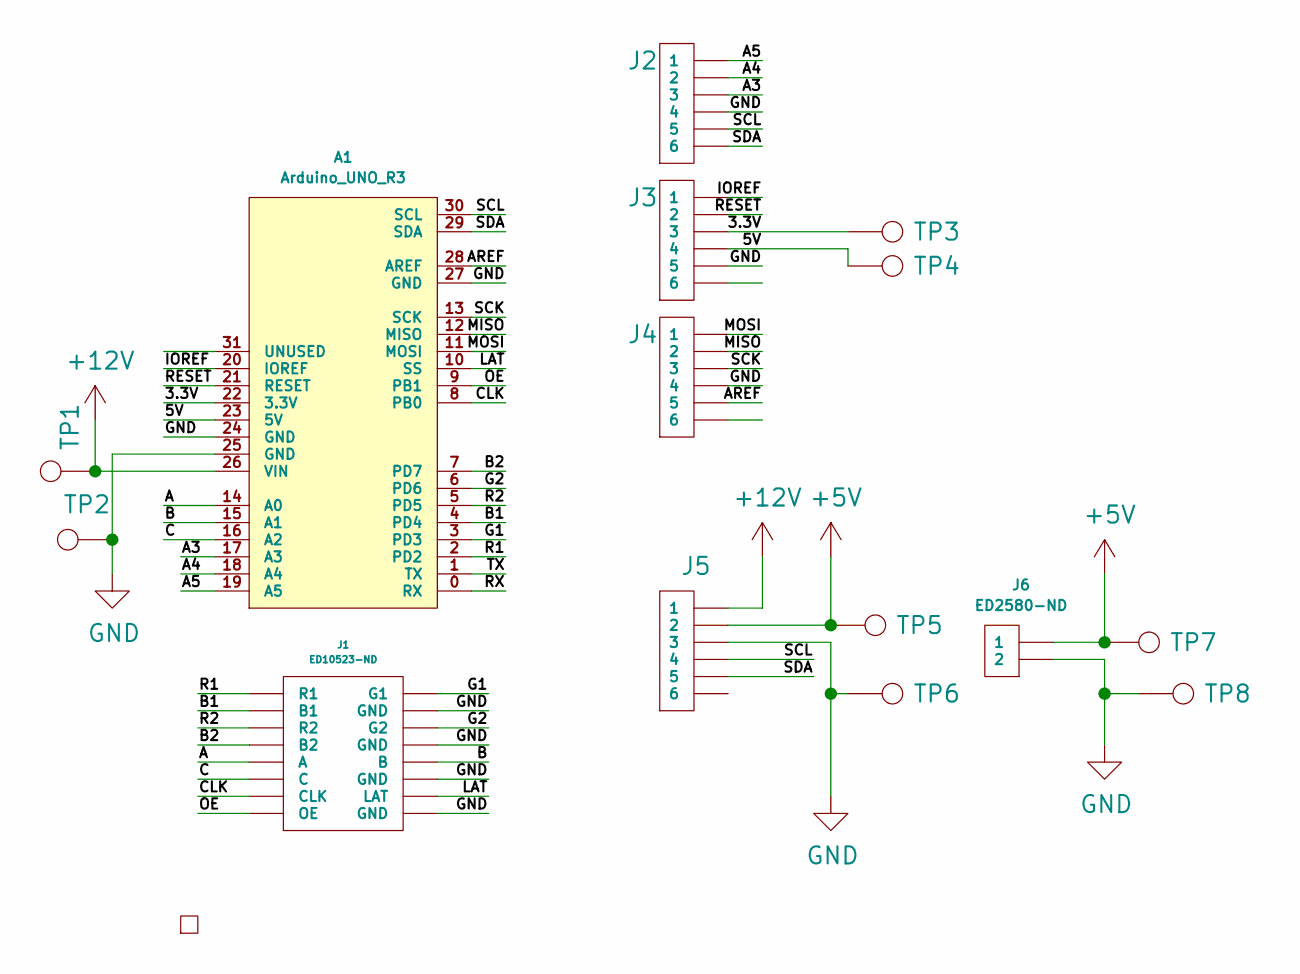
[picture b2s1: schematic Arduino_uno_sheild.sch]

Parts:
A1: Arduino_UNO_R3; Arduino Uno Sheild
J1: ED10523-ND; 16 pos 3M connector
J2, J3, J4: 6posheader; 6 pos header pin
J5: 6posheader; 455-1708-ND
J6: ED2580-ND; ED1501-ND
TP1, TP2, TP3, TP4, TP5, TP6, TP7, TP8: TestPoint; TestPoint_Pad_1.0x1.0mm
y1: rover_silkscreen; rover_image

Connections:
+5V: J5.2, J6.1, TP5.1, TP7.1
+12V: A1.26 (VIN), J5.1, TP1.1
/3.3V: A1.22 (3.3V), J3.3, TP3.1
/5V: A1.23 (5V), J3.4, TP4.1
/A: A1.14 (A0), J1.9 (A)
/A3: A1.17 (A3), J2.3
/A4: A1.18 (A4), J2.2
/A5: A1.19 (A5), J2.1
/AREF: A1.28 (AREF), J4.5
/B: A1.15 (A1), J1.10 (B)
/B1: A1.4 (PD4), J1.3 (B1)
/B2: A1.7 (PD7), J1.7 (B2)
/C: A1.16 (A2), J1.11 (C)
/CLK: A1.8 (PB0), J1.13 (CLK)
/G1: A1.3 (PD3), J1.2 (G1)
/G2: A1.6 (PD6), J1.6 (G2)
/IOREF: A1.20 (IOREF), J3.1
/LAT: A1.10 (SS), J1.14 (LAT)
/MISO: A1.12 (MISO), J4.2
/MOSI: A1.11 (MOSI), J4.1
/OE: A1.9 (PB1), J1.15 (OE)
/R1: A1.2 (PD2), J1.1 (R1)
/R2: A1.5 (PD5), J1.5 (R2)
/RESET: A1.21 (RESET), J3.2
/RX: A1.0 (RX)
/SCK: A1.13 (SCK), J4.3
/SCL: A1.30 (SCL), J2.5, J5.4
/SDA: A1.29 (SDA), J2.6, J5.5
/TX: A1.1 (TX)
GND: A1.24 (GND), A1.25 (GND), A1.27 (GND), J1.4 (GND), J1.8 (GND), J1.12 (GND), J1.16 (GND), J2.4, J3.5, J4.4, J5.3, J6.2, TP2.1, TP6.1, TP8.1
